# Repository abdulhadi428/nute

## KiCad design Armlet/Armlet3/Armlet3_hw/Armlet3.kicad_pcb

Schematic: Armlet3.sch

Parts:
ANT1: ANT_PCB_MONO
BZ1: BUZZER
C1: 100pF
C2, C4: 1.5pF
C3: 1pF
C5, C8, C62: 3.3pF
C6, C11: 220pF
C7, C9, C12, C15: 10n
C10, C14, C45, C46, C60, C61: 0.1u
C13: 47n
C16, C17: 10pF; CAP_0402
C18, C22, C23, C25, C30, C32, C33, C34, C51, C56, C57: 0.1u; CAP_0603
C19: 1u; CAP_0603
C20, C21, C38, C39, C40, C42, C43, C44, C47, C52: 0.1u; CAP_0402
C24, C31, C35, C41: 10u; CAP_0805
C26, C27, C50: 10u
C28, C48, C64: 1u
C29: DNM
C36, C37, C55: 20pF; CAP_0402
C49, C54: 1u; CAP_0402
C53: 100pF; CAP_0402
C58: 150pF; CAP_0402
C59: 1n; CAP_0402
C63: 6.8pF
D2: LED
D3: PMLL4148
DA1: DNM
DA2: VS1011
DA3: MAX4453
DA4: MCP73832
DA5: NCP583SQ
DD1: CC1101
DD2: STM32F205VX-100
DD3: MMA8452Q
HOLE1, HOLE2: HOLE_METALLED
L1, L6: 18nH; IND_0402
L2, L3, L4, L5: 12nH; IND_0402
L7: 100uH; IND_1812
L8: 15nH; IND_0402
M1: MOTOR
Q1, Q2, Q6: MMBT2222
Q3: TSOP75256
Q4: IRLML9303
Q5: BC848CL
Q7: DNM
R1: 56k
R2, R3: 4k7
R4, R5, R39: 1k
R6, R11: 20
R7, R9: 330k
R8: 10
R10: 2k
R12: 15R; RES_0603
R13: 150; RES_0603
R14: 220R; RES_0402
R15, R16: DNM; RES_0402
R17, R26, R27, R30, R32, R34: 10k; RES_0402
R18: 51R; RES_0402
R19, R29, R35: 1k; RES_0402
R20: 100
R21: 150; RES_0402
R25: 100; RES_0402
R28, R33: 1k; RES_0603
R36: 20k; RES_0402
R37: 330k; RES_0402
R40, R41: 4K7; RES_0402
SW1, SW2, SW3, SW4, SW5, SW6, SW7, SW8, SW9: BUTTON
TP2, TP3: TESTPOINT
VCap1, VCap2: 2.2u; CAP_0402
XL1: CONN_NOKIA_LCD24
XL2: CONN_AUDIO_SIMPLE
XL3, XL4: CONN_4
XL5: CONN_3
XL6: ST_SWD
XL7: CONN_1
XL8: CONN_MICROSD
XL10: USB_MICRO_B
XL11: CONN_NOKIA_BAT
XTAL1: 27MHz; 03225
XTAL2: 12.0MHz; 0532

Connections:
+3.3V: C6.1, C7.1, C8.1, C9.1, C10.1, C11.1, C18.1, C19.1, C20.1, C21.1, C23.1, C25.1, C29.1, C30.1, C31.1, C32.1, C33.1, C34.1, C35.1, C38.1, C39.1, C40.1, C41.1, C42.1, C44.1, C47.1, C49.1, C50.1, C60.1, C64.1, DA1.3 (Vout), DA2.6 (DVDD0), DA2.14 (DVDD1), DA2.19 (DVDD2), DA2.32 (TEST), DA2.38 (AVDD0), DA2.43 (AVDD1), DA2.45 (AVDD2), DA5.3 (Vout), DD1.4 (DVDD), DD1.9 (AVDD), DD1.11 (AVDD), DD1.14 (AVDD), DD1.15 (AVDD), DD1.18 (DGUARD), DD2.6, DD2.11, DD2.19, DD2.22, DD2.28, DD2.50, DD2.75, DD2.100, DD3.1 (VDDIO), DD3.14 (VDD), Q4.2 (S), R2.1, R3.2, R18.1, XL1.3 (VDDI), XL1.7 (PAR/~SPI), XL1.22 (Vdd), XL6.1 (Vdd)
+5V: C27.1, C28.1, DA1.1 (EN), DA1.4 (Vin), DA4.4 (VDD), R15.2, R19.2, XL10.1 (UVcc)
+BATT: BZ1.1, C24.1, C26.1, C48.1, DA4.3 (VBAT), DA5.4 (Vin), M1.2 (-), R7.1, R17.2, R21.2, XL11.1 (+)
/12MHz_Clk: DA2.18 (XTALI), DD2.67
/ACC_IRQ: DD2.17, DD3.11 (INT1)
/Btn1: DD2.81, SW1.2
/Btn2: DD2.82, SW2.2
/Btn3: DD2.84, SW3.2
/Btn4: DD2.85, SW4.2
/Btn5: DD2.88, SW5.2
/Btn6: DD2.55, SW6.2
/Btn7: DD2.56, SW7.2
/Btn8: DD2.57, SW8.2
/Btn9: DD2.58, SW9.2
/Buzzer: DD2.59, R5.1
/BuzzerOut: BZ1.2, Q2.3 (C)
/CC_CS: DD1.7 (CSn), DD2.69
/CC_GDO0: DD1.6 (GDO0), DD2.29, TP2.1
/CC_GDO2: DD1.3 (GDO2), DD2.26, TP3.1
/CC_MISO: DD1.2 (SO(GDO1)), DD2.31
/CC_MOSI: DD1.20 (SI), DD2.32
/CC_SCK: DD1.1 (SCLK), DD2.30
/Charge: DA4.1 (STAT), DD2.18
/I2C_SCL: DD2.92, DD3.4 (SCL), R2.2
/I2C_SDA: DD2.93, DD3.6 (SDA), R3.1
/LCD_BCKLT: DD2.96, R12.2
/LCD_DA0: DD2.97, XL1.6 ((SDA)DA0)
/LCD_DA1: DD2.98, XL1.18 (DA1)
/LCD_DA2: DD2.1, XL1.8 (DA2)
/LCD_DA3: DD2.2, XL1.17 (DA3)
/LCD_DA4: DD2.3, XL1.9 (DA4)
/LCD_DA5: DD2.4, XL1.15 (DA5)
/LCD_DA6: DD2.5, XL1.10 (DA6)
/LCD_DA7: DD2.38, XL1.14 (DA7)
/LCD_DC: DD2.39, XL1.19 ((SCLK)D/~C)
/LCD_RD: DD2.41, XL1.20 (~RD)
/LCD_WR: DD2.40, XL1.5 (~WR)
/LCD_XCS: DD2.42, XL1.11 (CS)
/LCD_XRES: DD2.43, XL1.12 (ResX)
/P_SCL: DD2.47, R40.1, XL3.2 (PM), XL4.2 (PM)
/P_SDA: DD2.48, R41.1, XL3.4, XL4.4
/PeriphPwr: DD2.51, R13.2, R40.2, R41.2
/PeriphPwr1: R13.1, XL3.1, XL4.1
/RF1: DD1.12 (RF_P), L2.2
/RF2: DD1.13 (RF_N), L5.2
/RX2: DD2.87, XL5.3
/SD_CLK: DD2.80, XL8.5 (SCK/CLK)
/SD_CMD: DD2.83, XL8.3 (MOSI/CMD)
/SD_DAT0: DD2.65, XL8.7 (MISO/DAT0)
/SD_DAT1: DD2.66, XL8.8 (DAT1)
/SD_DAT2: DD2.78, XL8.1 (DAT2)
/SD_DAT3: DD2.79, XL8.2 (~SS~/DAT3)
/SD_POWER: DD2.33, Q4.1 (G)
/SD_VDD: C46.1, Q4.3 (D), XL8.4 (VDD)
/SND_C: DA2.42 (GBUF), R8.2, XL2.1 (COM)
/SND_L: DA2.46 (LEFT), R11.2, XL2.3 (L_IN)
/SND_R: DA2.39 (RIGHT), R6.2, XL2.2 (R_IN)
/SWCLK: DD2.76, XL6.2 (SWCLK)
/SWDIO: DD2.72, XL6.4 (SWDIO)
/TX2: DD2.86, XL5.2 (PM)
/UBat_2: DD2.15, R7.2, R9.1
/USB_DM: DD2.70, XL10.2 (D-)
/USB_DP: DD2.71, XL10.3 (D+)
/VS_DREQ: DA2.8 (DREQ), DD2.35
/VS_RST: DA2.3 (~xRESET), DD2.90
/VS_SCLK: DA2.28 (SCLK), DD2.52
/VS_SI: DA2.29 (SI), DD2.54
/VS_SO: DA2.30 (SO), DD2.53
/VS_XCS: DA2.23 (~xCS), DD2.89
/VS_XDCS: DA2.13 (~xDCS~/BSYNC), DD2.95
/Vibro: DD2.45, R4.1
/VibroOut: M1.1 (+), Q1.3 (C)
/XLed1: D2.A, R21.1
/XLed2: D2.C, Q6.3 (C)
/XotarIn: DD2.63, Q3.3 (OUT)
/XotarLED: DD2.64, R39.1
/XotarPower: DD2.34, R20.1
/klNFCModulation: DD2.23, DD2.77
/klNFC_Rx: C55.2, DD2.24, Q5.3 (C), R27.1
/klNFC_Tx: C52.2, DD2.25, R29.1
/klNFC_Vcc: C56.1, DD2.16, R25.2, R27.2, R28.1
AGND: C57.1, DA3.3, DA3.5, R28.2, R33.1, R34.1
GND: C1.1, C4.2, C5.2, C6.2, C7.2, C8.2, C9.2, C10.2, C11.2, C12.1, C13.1, C14.2, C15.1, C16.2, C17.2, C18.2, C19.2, C20.2, C21.2, C22.2, C23.2, C24.2, C25.2, C26.2, C27.2, C28.2, C29.2, C30.2, C31.2, C32.2, C33.2, C34.2, C35.2, C36.2, C37.2, C38.2, C39.2, C40.2, C41.2, C42.2, C43.2, C44.2, C45.2, C46.2, C47.2, C48.2, C49.2, C50.2, C51.2, C56.2, C57.2, C58.2, C59.2, C60.2, C61.2, C62.2, C63.2, C64.2, DA1.2 (GND), DA2.4 (DGND0), DA2.16 (DGND1), DA2.20 (DGND2), DA2.21 (DGND3), DA2.22 (DGND4), DA2.37 (AGND0), DA2.40 (AGND1), DA2.41 (AGND2), DA2.47 (AGND3), DA3.4, DA4.2 (GND), DA5.2 (GND), DD1.16 (GND), DD1.19 (GND), DD1.PAD (GND), DD2.10, DD2.20, DD2.27, DD2.74, DD2.94, DD3.5 (GND), DD3.7 (SA0), DD3.10 (GND), DD3.12 (GND), HOLE1.Hle, HOLE2.Hle, L7.2, Q1.2 (E), Q2.2 (E), Q3.1 (GND), Q3.4 (GND), Q5.2 (E), Q6.2 (E), Q7.2 (E), R1.2, R9.2, R10.2, R16.1, R26.2, R33.2, R35.1, SW1.1, SW2.1, SW3.1, SW4.1, SW5.1, SW6.1, SW7.1, SW8.1, SW9.1, VCap1.2, VCap2.2, XL1.1 (GND), XL1.2 (LED-), XL1.4 (GND), XL1.16 (GND), XL1.21 (GND), XL1.24 (GND), XL1.H (Case), XL2.H, XL3.3, XL4.3, XL5.1, XL6.3 (GND), XL8.6 (GND), XL8.H (Housing), XL10.4 (UGND), XL10.5 (UID), XL10.SHLD, XL11.3 (GND), XTAL1.H, XTAL2.H
unnamed: C53.1, DA3.1, R36.2
unnamed: DA3.2, R29.2, R36.1
unnamed: C52.1, C58.1, L7.1
unnamed: C22.1, DA2.44 (RCAP)
unnamed: C2.1, L3.2, L6.1
unnamed: Q6.1 (B), R39.2
unnamed: C59.1, D3.C, R26.1, R32.1
unnamed: C54.2, D3.A, R35.2
unnamed: C54.1, DA3.7, R37.2
unnamed: DA3.6, R30.2, R37.1
unnamed: Q2.1 (B), R5.2
unnamed: C1.2, L1.1
unnamed: C3.2, C4.1, L5.1, L6.2
unnamed: C2.2, C3.1, L1.2, L2.1
unnamed: Q1.1 (B), R4.2
unnamed: C62.1, L4.1, L8.2
unnamed: ANT1.1, C63.1, L8.1
unnamed: C14.1, DD1.5 (DCOUPL)
unnamed: DD2.61, XL7.1
unnamed: DD1.17 (RBIAS), R1.1
unnamed: C17.1, DD1.10 (XOSC_Q2), XTAL1.2
unnamed: DD2.13, R14.1
unnamed: C15.2, R11.1
unnamed: C12.2, R6.1
unnamed: C13.2, R8.1
unnamed: DA4.5 (PROG), R10.1
unnamed: R12.1, XL1.23 (LED+)
unnamed: DD2.73, VCap2.1
unnamed: C37.1, R14.2, XTAL2.2
unnamed: C36.1, DD2.12, XTAL2.1
unnamed: C16.1, DD1.8 (XOSC_Q1), XTAL1.1
unnamed: C5.1, L3.1, L4.2
unnamed: C61.1, DD3.2 (BYP)
unnamed: C55.1, Q5.1 (B), R32.2
unnamed: DD2.49, VCap1.1
unnamed: DA5.1 (EN), Q7.3 (C), R17.1
unnamed: Q7.1 (B), R15.1, R16.2
unnamed: C45.1, Q3.2 (Vs), R20.2
unnamed: C51.1, DA3.8, R25.1
unnamed: C53.2, R30.1, R34.2
unnamed: C43.1, DD2.21, R18.2
unnamed: DD2.68, R19.1

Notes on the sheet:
Accelerometer I2C addr = 0x1C
USB connect detector
Peripheral I2C Pull-Ups
Pill Connectors
T2C3
USART4 RX
USART4 TX
T2C1/T2ETR
DEBUG TX/RX
USB
Connectors
Radio
CPU
I2C and Accelerometer
Xotar in & out
Vibro & buzzer
klNFC
Nokia battery connector
20pF cap removes remains of carrier
Note AGND here ^^^
Half-Vcc divider
100pF & 10k => f0=160 kHz
Programming
Peripherals usage SDIO - SD Card USB UART2 - debug output UART4 - klNFC SPI1 - CC (Radio) Bus SPI2 - Audio Bus TIM1 Ch4 - Vibro TIM2 Ch3 - klNFC TX TIM2 ETR - klNFC modulation in TIM3 Ch2 - Xotar LED TIM4 Ch1 - Buzzer TIM5 - Xotar Data timings TIM8 Ch1 - Xotar In TIM10 Ch1 - LCD backlight EXTI0 - V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
Audio
Buttons
SD card
I2C pull-ups
3.3V 150mA power regulator
Li-Ion charger 2k => 0.5 A
Battery meter
Power
LCD
Matching circuit
Debug connector

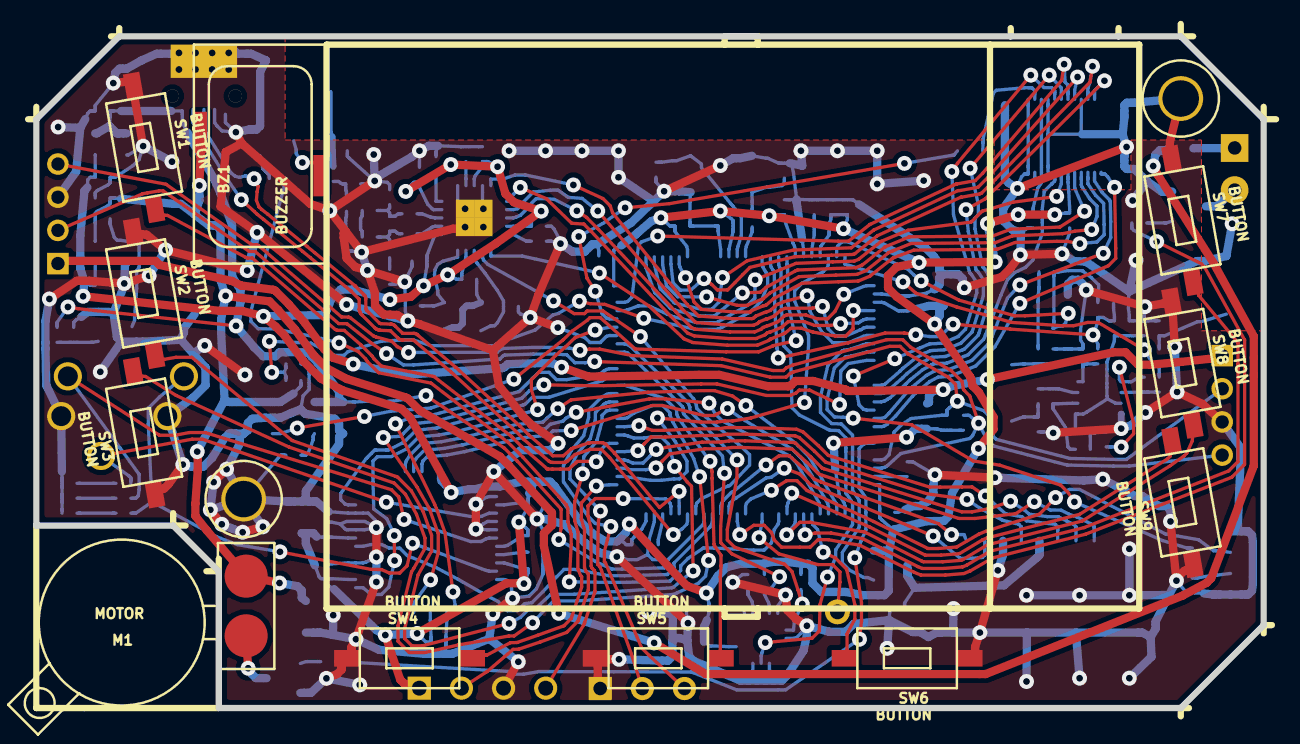
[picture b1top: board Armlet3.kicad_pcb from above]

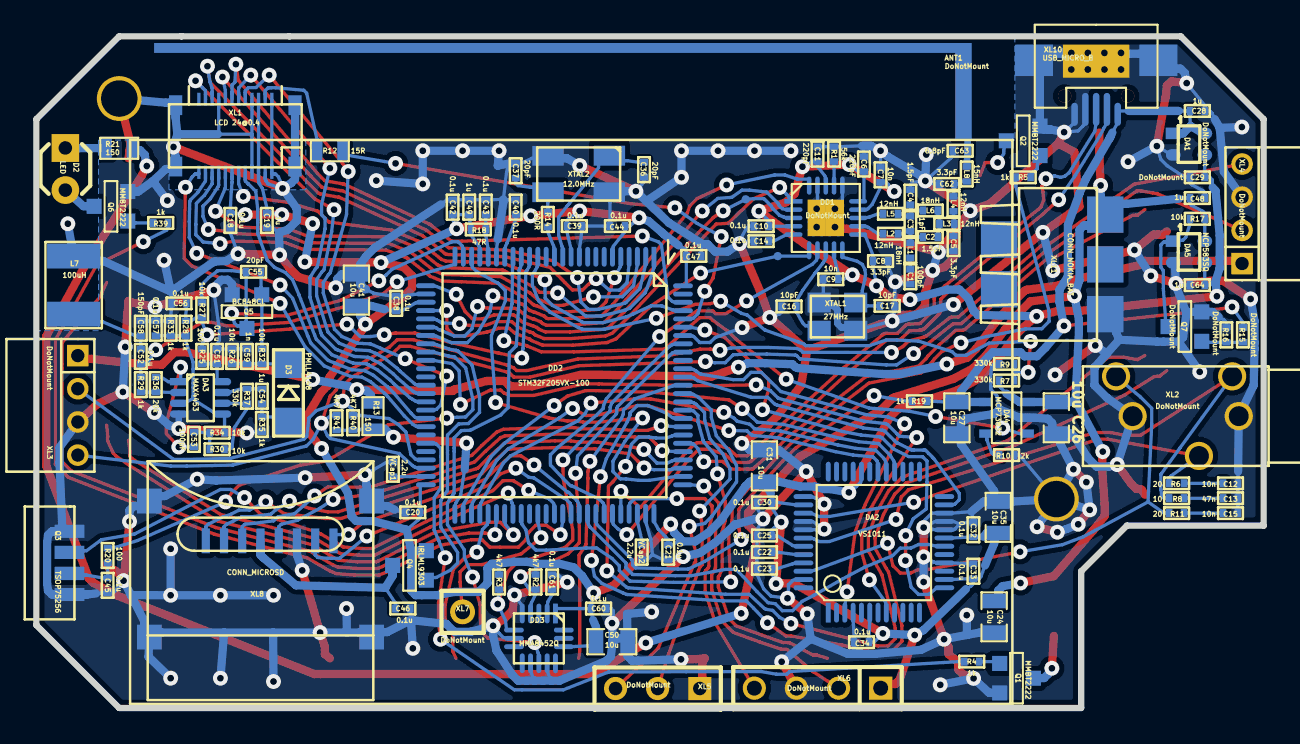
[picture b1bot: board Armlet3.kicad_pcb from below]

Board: 2 copper layers, 74.0 x 40.5 mm, 155 parts (142 on the bottom side), 125 nets.

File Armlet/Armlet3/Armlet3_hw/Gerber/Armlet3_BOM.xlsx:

Document version | Armlet_BOM v.20130328.2012
Reference | Footprint | Value | Item count | Description | Solder Point per cmp | SolderPoint total
Микросхемы
DA1 | SC-82AB | Do not mount
DA2 | LQFP48 | VS1011E-L | 1 | Предоставим в трее | 48 | 48
DA3 | SOT23-8 | MAX4453 | 1 | Предоставим в ленте | 8 | 8
DA4 | SOT23-5 | MCP73832T-2ACI/OT | 1 | Предоставим в ленте | 5 | 5
DA5 | SC-82AB | NCP583SQ33T1G | 1 | Предоставим в ленте | 4 | 4
DD1 | QFN20 | Do not mount
DD2 | LQFP100 | STM32F205VET6-100 | 1 | Предоставим в трее | 100 | 100
DD3 | QFN16_5 | Do not mount
Активные компоненты
Q4 | SOT23 | IRML9303 | 1 | Предоставим в ленте | 3 | 3
Q5 | SOT23 | BC848CL | 1 | Предоставим в ленте | 3 | 3
Q1, Q2, Q6 | SOT23 | MMBT2222 | 3 | Предоставим в ленте | 3 | 9
Q3 | TSOP75256 | TSOP75256 | 1 | Предоставим в ленте | 4 | 4
Q7 | SOT23 | Do not mount
D2 | Выводной | Do not mount
D3 | SOD80C | PMLL4148 | 1 | Предоставим в ленте | 2 | 2
Пассивные компоненты
XTAL1 | SMD3225 | 27MHz | 1 | Предоставим в ленте | 4 | 4
XTAL2 | SMD0532 | 12MHz | 1 | Предоставим в ленте | 4 | 4
Конденсаторы
C3 | CAP_0402 | 1pF NPO | 1 | Предоставим в ленте | 2 | 2
C2, C4 | CAP_0402 | 1.5pF NPO | 2 | Предоставим в ленте | 2 | 4
C5, C8, C62 | CAP_0402 | 3.3pF NPO | 3 | Предоставим в ленте | 2 | 6
C63 | CAP_0402 | 6.8pF NPO | 1 | Предоставим в ленте | 2 | 2
C16, C17 | CAP_0402 | 10pF NPO | 2 | Предоставим в ленте | 2 | 4
C36, C37, C55 | CAP_0402 | 20pF NPO | 3 | Предоставим в ленте | 2 | 6
C1, C53 | CAP_0402 | 100pF NPO | 2 | Предоставим в ленте | 2 | 4
C58 | CAP_0402 | 150pF NPO | 1 | Предоставим в ленте | 2 | 2
C6, C11 | CAP_0402 | 220pF | 2 | Предоставим в ленте | 2 | 4
C59 | CAP_0402 | 1n | 1 | Предоставим в ленте | 2 | 2
C7, C9, C12, C15 | CAP_0402 | 10n | 4 | Предоставим в ленте | 2 | 8
C13 | CAP_0402 | 47n | 1 | Предоставим в ленте | 2 | 2
C10, C14, C18, C20, C21, C22, C23, C25, C30, C32, C33, C34, C38, C39, C40, C42,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 | CAP_0402 | 0.1u | 27 | Предоставим в ленте | 2 | 54
C19, C28, C48, C49, C54, C64 | CAP_0402 | 1u | 6 | Предоставим в ленте | 2 | 12
VCap1, VCap2 | CAP_0402 | 2.2u | 2 | Предоставим в ленте | 2 | 4
C24, C26, C27, C31, C35, C41, C50 | CAP_0805 | 10u | 7 | Предоставим в ленте | 2 | 14
C29 | CAP_0402 | Do not mount
Резисторы
R8 | RES_0402 | 10R | 1 | Предоставим в ленте | 2 | 2
R12 | RES_0603 | 15R | 1 | Предоставим в ленте | 2 | 2
R6, R11 | RES_0402 | 20R | 2 | Предоставим в ленте | 2 | 4
R18 | RES_0402 | 51R | 1 | Предоставим в ленте | 2 | 2
R20, R25 | RES_0402 | 100R | 2 | Предоставим в ленте | 2 | 4
R13, R21 | RES_0603 | 150R | 2 | Предоставим в ленте | 2 | 4
R4, R5, R19, R28, R29, R33, R35, R39 | RES_0402 | 1k | 8 | Предоставим в ленте | 2 | 16
R10 | RES_0402 | 2k | 1 | Предоставим в ленте | 2 | 2
R2, R3, R40, R41 | RES_0402 | 4k7 | 4 | Предоставим в ленте | 2 | 8
R17, R26, R27, R30, R32, R34 | RES_0402 | 10k | 6 | Предоставим в ленте | 2 | 12
R36 | RES_0402 | 20k | 1 | Предоставим в ленте | 2 | 2
R1 | RES_0402 | 56k | 1 | Предоставим в ленте | 2 | 2
R14 | RES_0402 | 220R | 1 | Предоставим в ленте | 2 | 2
R7, R9, R37 | RES_0402 | 330k | 3 | Предоставим в ленте | 2 | 6
R15, R16 | RES_0402 | Do not mount
Индуктивности
L2, L3, L4, L5 | IND_0402 | 12nH | 4 | Предоставим в ленте | 2 | 8
L1, L6 | IND_0402 | 18nH | 2 | Предоставим в ленте | 2 | 4
L7 | IND_1812 | 100uH | 1 | Предоставим в ленте | 2 | 2
L8 | IND_0402 | 15nH | 1 | Предоставим в ленте | 2 | 2
Разъемы
XL1 | LCD_24_04 | LCD 24@0.4 | 1 | Предоставим в ленте | 28 | 28
XL2 |  | Do not mount
XL3, XL4 | PBS2-04R | Do not mount
XL8 | 8pin_cap_fix05 | uSD holder | 1 | Предоставим в ленте | 12 | 12
XL11 | BAT_CONT | Batt contacts | 1 | Предоставим в ленте | 5 | 5
XL10 | USB_MICRO_B | uUSB connector | 1 | Предоставим в ленте | 10 | 10
 |  |  |  |  | Solder points per brd | 463

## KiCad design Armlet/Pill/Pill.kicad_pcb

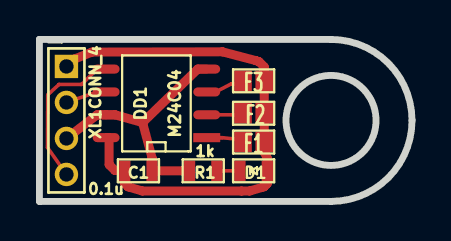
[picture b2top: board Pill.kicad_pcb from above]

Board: 2 copper layers, 20.7 x 9.0 mm, 8 parts (0 on the bottom side), 8 nets.

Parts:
C1: 0.1u; CAP_0603
D1: LED; LED0603
DD1: M24C04; SO8E
F1, F2, F3: FUSE0R; SMD0603_FUSE
R1: 1k; RES_0603
XL1: CONN_4; CONN_2MM_1X4

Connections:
+3.3V: C1.1, D1.A, DD1.8, F1.2, F2.2, F3.2, XL1.1
/1: DD1.1, F1.1
/2: DD1.2, F2.1
/3: DD1.3, F3.1
/I2C_SCL: DD1.6, XL1.2
/I2C_SDA: DD1.5, XL1.4
GND: C1.2, DD1.4, DD1.7, R1.2, XL1.3
unnamed: D1.C, R1.1

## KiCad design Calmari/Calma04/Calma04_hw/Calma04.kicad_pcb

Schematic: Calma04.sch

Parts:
C1, C2, C3, C4, C5: 0.1u; CAP_0603
C6, C8, C12: 0.1u
C7, C9, C11, C13, C14, C15: 10u
C10: 1u; CAP_0603
D1: SS14
DA1: TPS61042
DA2: NCP583SQ
DA3: MCP73832
DD1: STM32F100C4
F1, F2: FUSE0R
HOLE2: HOLE_METALLED
L1: 6.8uH; IND_1210
Q1: ALS-PT19-315C
R1, R2: 330k; RES_0603
R3: 13R; RES_0603
R4: 2k
R5, R6: 10k; RES_0603
R7: 120k; RES_0603
SW1: SWITCH
SW2: BUTTON
TP1: TESTPOINT
XL1: CONN_3
XL2: ST_SWD
XL3, XL4, XL8, XL9, XL10, XL11, XL12, XL13: CONN_1
XL5, XL6: CONN_2
XL7: USB_MICRO_B

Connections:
+3.3V: C2.1, C3.1, C4.1, C5.1, C8.1, C9.1, C10.1, DA2.3 (Vout), DD1.1 (VBAT), DD1.9 (VDDA), DD1.24 (VDD1), DD1.36 (VDD2), DD1.48 (VDD3), F2.2, Q1.1, XL2.1 (Vdd)
+5V: C14.1, DA3.4 (VDD), XL7.1 (UVcc)
+BATT: C6.1, C7.1, C12.1, C13.1, C15.1, DA1.3 (Vin), DA2.1 (EN), DA2.4 (Vin), DA3.3 (VBAT), F1.2, F2.1, L1.2, R2.1, SW1.2, XL10.1, XL11.1
/BAT_IN: F1.1, SW1.1, XL3.1
/BTN: DD1.10 (ADC1-0/WKUP/PA0), SW2.1, XL6.1
/Charge: DA3.1 (STAT), DD1.17 (ADC1-7/T3C2/MOSI1/PA7), XL8.1, XL9.1
/FB: DD1.14 (ADC1-4/DAC1/CK2/PA4), R7.2
/RX: DD1.31 (T1C3/RX1/PA10), XL1.1
/SB_SWCLK: DD1.37 (SWCLK/(JTCK)/(PA14)), XL2.2 (SWCLK)
/SB_SWDAT: DD1.34 (SWDIO/(JTMS)/(PA13)), XL2.4 (SWDIO)
/TX: DD1.30 (T1C2/TX1/PA9), XL1.2 (PM)
GND: C1.2, C2.2, C3.2, C4.2, C5.2, C6.2, C7.2, C8.2, C9.2, C10.2, C11.2, C12.2, C13.2, C14.2, C15.2, DA1.6 (GND), DA1.PAD (GND), DA2.2 (GND), DA3.2 (GND), DD1.8 (VSSA), DD1.23 (VSS1), DD1.35 (VSS2), DD1.44 (BOOT0), DD1.47 (VSS3), HOLE2.Hle, R1.2, R3.2, R4.2, R5.2, SW2.2, XL1.3, XL2.3 (GND), XL4.1, XL6.2 (PM), XL7.4 (UGND), XL7.5 (UID), XL7.SHLD, XL12.1, XL13.1
unnamed: C1.1, DD1.19 (PB1/T3C4/ADC1-9), Q1.2, R5.1
unnamed: DD1.7 (NRST), TP1.1
unnamed: DD1.18 (PB0/T3C3/ADC1-8), R1.1, R2.2
unnamed: DA3.5 (PROG), R4.1
unnamed: DA1.4 (FB), R6.2, R7.1
unnamed: DA1.2 (Rs), R3.1, R6.1
unnamed: DA1.5 (CTRL), DD1.11 (ADC1-1/T2C2/PA1)
unnamed: DA1.1 (LED), XL5.2 (PM)
unnamed: C11.1, D1.C, DA1.7 (OVP), XL5.1
unnamed: D1.A, DA1.8 (SW), L1.1

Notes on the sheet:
-BATTERY
+BATTERY
In case of 2xAA, no LDO is required. Solder fuse instead.
Battery measurement
LEDs (4...8)
Choose capacitor max voltage carefully (30v recommended)
Button
R=252/Iled[mA]
Li-Ion charger 2k => 0.5 A
USB
Connectors for spliting pcb

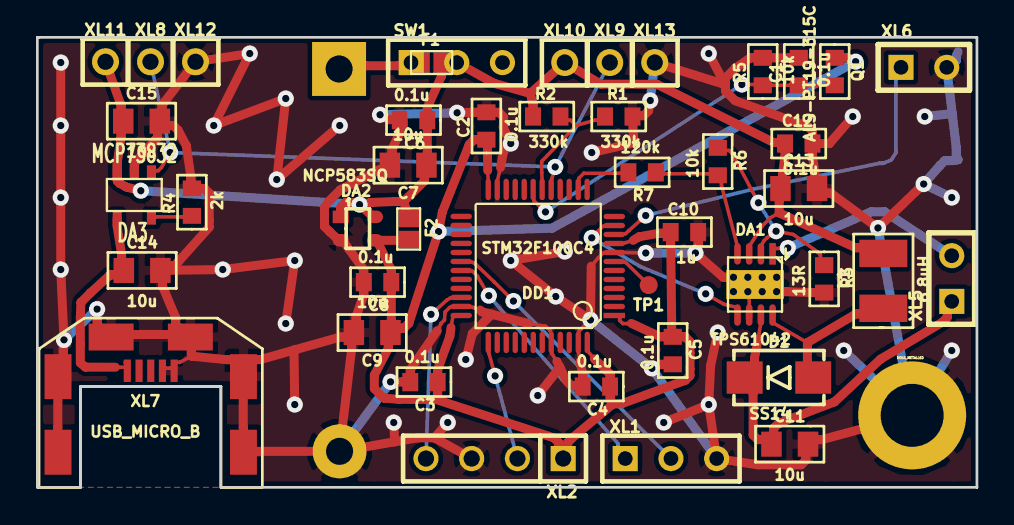
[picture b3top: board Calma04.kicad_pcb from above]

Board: 2 copper layers, 52.2 x 25.0 mm, 48 parts (1 on the bottom side), 22 nets.

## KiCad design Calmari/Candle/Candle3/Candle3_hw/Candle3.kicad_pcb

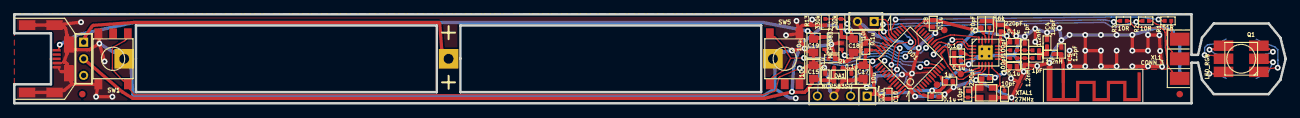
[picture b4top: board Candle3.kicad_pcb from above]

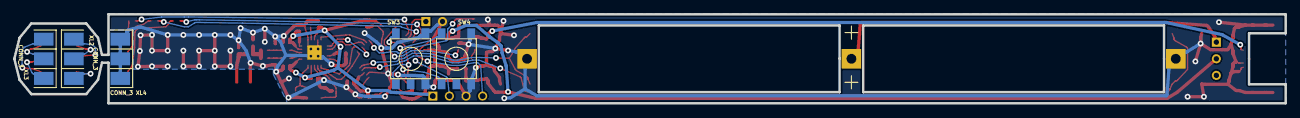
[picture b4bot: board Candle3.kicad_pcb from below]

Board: 2 copper layers, 194.4 x 13.6 mm, 63 parts (5 on the bottom side), 43 nets.

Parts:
ANT1: ANT_GENERAL; ANT_2400_MEANDER
C1, C3: 100pF; CAP_0402
C2, C6: 1pF; CAP_0402
C4: 1.8pF; CAP_0402
C5: 1.5pF; CAP_0402
C7, C13: 10pF; CAP_0402
C8, C9, C10, C11, C14, C16, C41, C51, C111, C141: 0.1u; CAP_0402
C12: 1u; CAP_0402
C15, C17, C18, C19: 10u; CAP_0805
C91, C151, C181: 220pF; CAP_0402
DA1: NCP583SQ; SC82AB
DA2: MCP73832; SOT23-5
DD1: STM32F100C4; LQFP48
DD2: CC2500; QFN20
L1, L2, L3: 1.2nH; IND_0402
Q1: LED_RGB; LED_HH5050_RGB
R1: 51R; RES_0402
R2, R3: 10R; RES_0402
R4: 2k; RES_0402
R6, R13: 330k; RES_0402
R171: 56k; RES_0402
RP1, RP2, RP3: REFPOINT; REF_POINT_1MM
SW1: SWITCH; SIL-3
SW2, SW3, SW4, SW5: BUTTON; BUTTON_6x6SMD
TP1, TP2: TESTPOINT; TESTPOINT_1MM
XL1, XL2, XL3, XL4: CONN_3; CONN_SOLDER3
XL5: ST_SWD; SIL-4
XL6: USB_MICRO_B; USBmicro_MOLEX_WM17142
XL7: CONN_2; SIL-2
XL9, XL15, XL16: CONN_1; SIL1_SQUARE_1MM5
XTAL1: 27MHz; CRYSTAL_03225C4

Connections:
+3.3V: C8.1, C9.1, C10.1, C11.1, C12.1, C16.1, C17.1, C41.1, C91.1, C111.1, C141.1, C151.1, C181.1, DA1.3, DD1.1, DD1.9, DD1.24, DD1.36, DD1.48, DD2.4, DD2.9, DD2.11, DD2.14, DD2.15, DD2.18, XL5.1
+5V: C19.1, DA2.4, XL6.1
+BATT: C14.1, C15.1, C18.1, DA1.1, DA1.4, DA2.3, R6.1, SW1.2
/Ant1: C1.1, DD2.12
/Ant2: C3.1, DD2.13
/BATTERY_PLUS: SW1.1, XL9.1
/BTN_DOWN: DD1.43, SW4.2
/BTN_PWR: DD1.10, SW2.2
/BTN_TX: DD1.11, SW5.2
/BTN_UP: DD1.42, SW3.2
/CC_CS: DD1.13, DD2.7
/CC_GDO0: DD1.14, DD2.6, TP1.1
/CC_MISO: DD1.16, DD2.2
/CC_MOSI: DD1.17, DD2.20
/CC_SCK: DD1.15, DD2.1
/Charge: DA2.1, DD1.25
/LED_B: DD1.32, R3.1
/LED_G: DD1.31, R2.1
/LED_R: DD1.29, R1.1
/SWCLK: DD1.37, XL5.2
/SWDIO: DD1.34, XL5.4
GND: ANT1.2, C4.2, C5.2, C6.2, C7.2, C8.2, C9.2, C10.2, C11.2, C12.2, C13.2, C14.2, C15.2, C16.2, C17.2, C18.2, C19.2, C41.2, C51.2, C91.2, C111.2, C141.2, C151.2, C181.2, DA1.2, DA2.2, DD1.8, DD1.23, DD1.35, DD1.44, DD1.47, DD2.16, DD2.19, DD2.PAD, L1.1, R4.2, R13.2, R171.2, SW2.1, SW3.1, SW4.1, SW5.1, XL4.1, XL4.2, XL4.3, XL5.3, XL6.4, XL6.5, XL6.SHLD, XL7.2, XL15.1, XL16.1, XTAL1.H
unnamed: DA2.5, R4.1
unnamed: Q1.RA, XL2.1
unnamed: Q1.GC, XL3.2
unnamed: Q1.RC, XL3.1
unnamed: Q1.BC, XL3.3
unnamed: Q1.GA, XL2.2
unnamed: Q1.BA, XL2.3
unnamed: R1.2, XL1.1
unnamed: R2.2, XL1.2
unnamed: R3.2, XL1.3
unnamed: C1.2, C2.1, L1.2
unnamed: DD1.7, TP2.1
unnamed: C3.2, C6.1, L3.2
unnamed: ANT1.1, C5.1, L2.1
unnamed: C2.2, C4.1, L2.2, L3.1
unnamed: DD1.30, XL7.1
unnamed: C13.1, DD2.10, XTAL1.2
unnamed: C7.1, DD2.8, XTAL1.1
unnamed: DD1.18, R6.2, R13.1
unnamed: DD2.17, R171.1
unnamed: C51.1, DD2.5

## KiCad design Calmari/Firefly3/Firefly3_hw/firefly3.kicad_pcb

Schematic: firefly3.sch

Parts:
C1, C2, C3, C4, C5: 0.1u; CAP_0603
C6, C8: 0.1u
C7, C9: 10u
C10: 1u; CAP_0603
D1: BAT54WS; SOD323
D2: LED
DA1: NCP1400
DD1: STM32F100C4
F1: FUSE0R
L1: 22uH
Q1: ALS-PT19-315C
Q2: LED_RGB 5050
R1, R3, R4: 51R; RES_0603
R2, R5: 10k; RES_0603
SW1: SWITCH
TP1: TESTPOINT
XL1: CONN_3
XL2: ST_SWD
XL3, XL4, XL6: CONN_1
XL5: CONN_8

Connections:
+3.3V: C2.1, C3.1, C4.1, C5.1, C8.1, C9.1, C10.1, D1.C, DA1.1 (CE), DA1.2 (OUT), DD1.1 (VBAT), DD1.9 (VDDA), DD1.24 (VDD1), DD1.36 (VDD2), DD1.48 (VDD3), Q1.1, XL2.1 (Vdd)
+BATT: C6.1, C7.1, F1.2, L1.2, R2.1, SW1.2
/2: DD1.43 (PB7/SDA1/T17C1N), XL5.2
/3: DD1.42 (PB6/SCL1/T16C1N), XL5.3
/4: DD1.39 ((PB3)/JTDO/(T2C2)), XL5.4
/5: DD1.14 (ADC1-4/DAC1/CK2/PA4), XL5.5
/6: DD1.15 (ADC1-5/DAC2/SCK1/PA5), XL5.6
/7: DD1.16 (ADC1-6/T3C1/MISO1/PA6), XL5.7
/8: DD1.17 (ADC1-7/T3C2/MOSI1/PA7), XL5.8
/BAT_IN: F1.1, SW1.1, XL3.1
/Lout: D1.A, DA1.5 (LX), L1.1
/RX: DD1.31 (T1C3/RX1/PA10), XL1.1
/SB_SWCLK: DD1.37 (SWCLK/(JTCK)/(PA14)), XL2.2 (SWCLK)
/SB_SWDAT: DD1.34 (SWDIO/(JTMS)/(PA13)), XL2.4 (SWDIO)
/TX: DD1.30 (T1C2/TX1/PA9), XL1.2 (PM)
GND: C1.2, C2.2, C3.2, C4.2, C5.2, C6.2, C7.2, C8.2, C9.2, C10.2, D2.C, DA1.4 (GND), DD1.8 (VSSA), DD1.23 (VSS1), DD1.35 (VSS2), DD1.44 (BOOT0), DD1.47 (VSS3), Q2.BC (B), Q2.GC (G), Q2.RC, R5.2, XL1.3, XL2.3 (GND), XL4.1, XL5.1, XL6.1
unnamed: DD1.18 (PB0/T3C3/ADC1-8), R2.2
unnamed: DD1.7 (NRST), TP1.1
unnamed: C1.1, DD1.19 (PB1/T3C4/ADC1-9), Q1.2, R5.1
unnamed: Q2.BA, R4.2
unnamed: DD1.13 (ADC1-3/T2C4/T15C2/RX2/PA3), R3.1
unnamed: DD1.12 (ADC1-2/T2C3/T15C1/TX2/PA2), R1.1
unnamed: DD1.11 (ADC1-1/T2C2/PA1), R4.1
unnamed: D2.A, Q2.RA, R1.2
unnamed: Q2.GA, R3.2

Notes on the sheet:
-BATTERY
+BATTERY

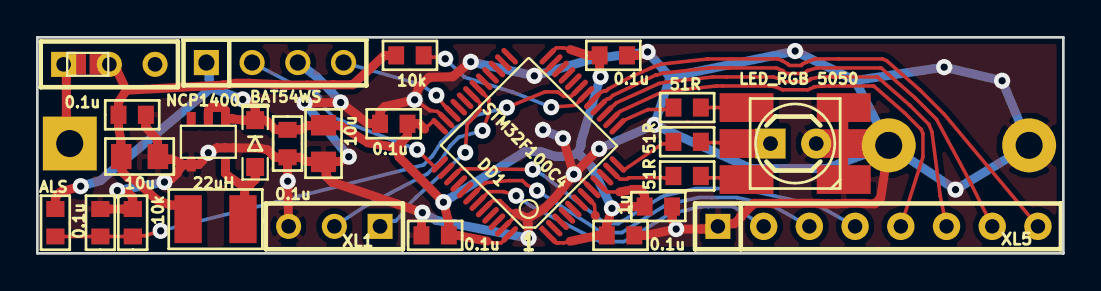
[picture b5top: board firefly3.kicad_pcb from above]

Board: 2 copper layers, 57.0 x 12.0 mm, 31 parts (0 on the bottom side), 25 nets.

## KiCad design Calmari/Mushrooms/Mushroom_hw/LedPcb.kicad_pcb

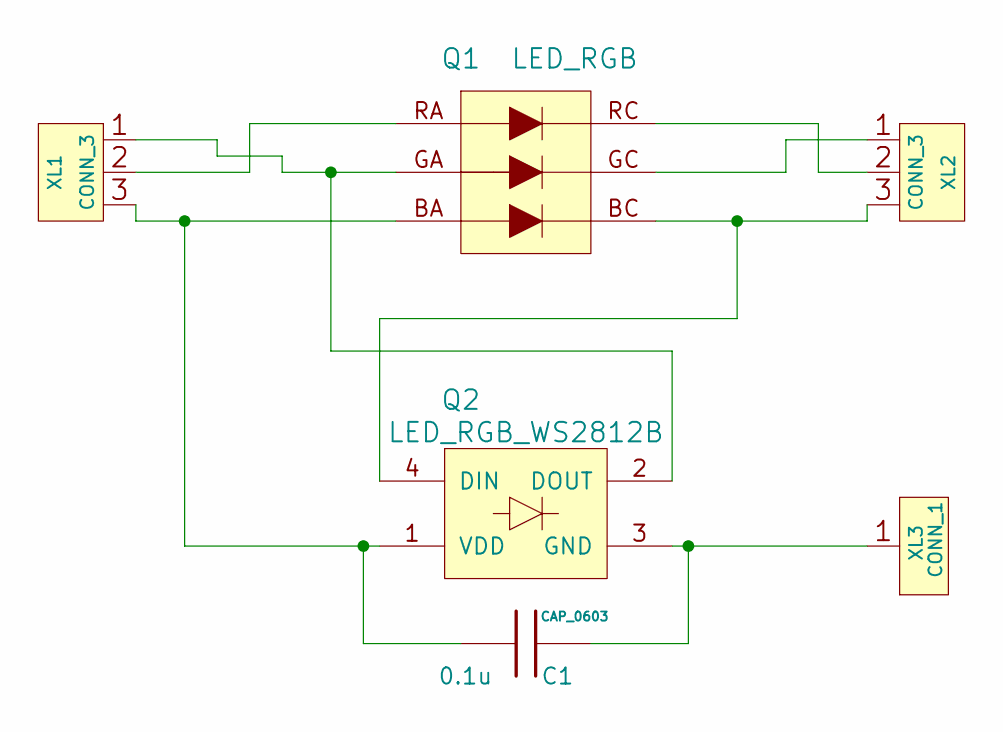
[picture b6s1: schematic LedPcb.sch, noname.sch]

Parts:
C1: 0.1u; CAP_0603
Q1: LED_RGB
Q2: LED_RGB_WS2812B
XL1, XL2: CONN_3
XL3: CONN_1

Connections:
unnamed: Q1.GA, Q2.2 (DOUT), XL1.1
unnamed: Q1.BC (B), Q2.4 (DIN), XL2.3
unnamed: Q1.RA, XL1.2 (PM)
unnamed: Q1.RC, XL2.2 (PM)
unnamed: Q1.GC (G), XL2.1
unnamed: C1.1, Q1.BA, Q2.1 (VDD), XL1.3
unnamed: C1.2, Q2.3 (GND), XL3.1

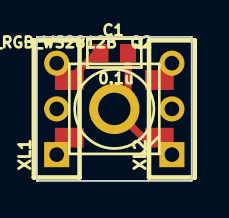
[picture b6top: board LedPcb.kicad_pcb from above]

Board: 2 copper layers, 8.6 x 8.0 mm, 6 parts (1 on the bottom side), 7 nets.

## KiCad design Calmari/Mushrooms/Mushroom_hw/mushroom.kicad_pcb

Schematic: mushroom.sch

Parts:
ANT1: ANT_PCB_NOCNTR
B1, B2, B3: BAT
C1, C6, C12, C14, C19, C20, C23, C24, C26: 0.1u
C2, C8, C11, C13, C15, C16, C21, C28: 10u
C3: 10u; CAP_0603
C4, C5, C7, C29, C30, C31: 0.1u; CAP_0603
C9: 10n; CAP_0603
C10: 1u; CAP_0603
C17, C18: 10pF; CAP_0603
C22, C25, C27: 220pF
D1, D2, D3: SS14
DA1, DA3, DA4: TPS61042
DA2: NCP583SQ
DD1: STM32L151CXTX
DD2: CC2500
F1, F2, F3, F4, F5, F6, F7, F8, F9, F10, F11, F12, F13, F14, F15, F16, F17, F18, F19, F20: FUSE0R
HOLE1, HOLE2, HOLE3, HOLE4: HOLE_METALLED
L1, L2, L3: 6.8uH; IND_1210
Q1, Q3, Q6: LED_RGB_WS2812B
Q2, Q4, Q5: LED_RGB
R1, R2: 4K7; RES_0402
R3, R8, R15: 100k
R4: 150; RES_0402
R5, R11, R16: 10k; RES_0603
R6, R12, R17: 13R; RES_0603
R7, R13, R18: 120k; RES_0603
R9, R10: 390k; RES_0603
R14: 56k
R19, R20, R21: 51R; RES_0603
RP1, RP2: REFPOINT
SW1: SWITCH_H
TP1, TP2, TP3: TESTPOINT
XL1, XL5, XL6, XL8, XL9, XL10, XL12, XL13, XL14, XL16, XL17, XL18, XL20, XL21, XL22, XL24: CONN_3
XL2: ST_SWD
XL3: CONN_4
XL4: CONN_4
XL7, XL11, XL15, XL19, XL23: CONN_1
XTAL1: 27MHz; 03225

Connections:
+3.3V: C3.1, C4.1, C5.1, C7.1, C9.1, C10.1, C12.1, C13.1, C22.1, C23.1, C24.1, C25.1, C26.1, C27.1, DA2.3 (Vout), DD1.1, DD1.9, DD1.24, DD1.36, DD1.48, DD2.4 (DVDD), DD2.9 (AVDD), DD2.11 (AVDD), DD2.14 (AVDD), DD2.15 (AVDD), DD2.18 (DGUARD), XL2.1 (Vdd)
+BATT: C1.1, C2.1, C6.1, C8.1, C14.1, C15.1, C20.1, C21.1, C29.1, C30.1, C31.1, DA1.3 (Vin), DA2.1 (EN), DA2.4 (Vin), DA3.3 (Vin), DA4.3 (Vin), L1.2, L2.2, L3.2, Q1.1 (VDD), Q3.1 (VDD), Q6.1 (VDD), R9.1, SW1.2, XL6.2 (PM), XL10.2 (PM), XL14.2 (PM), XL18.2 (PM), XL22.2 (PM)
/Ant: ANT1.1, ANT1.2, DD2.12 (RF_P), DD2.13 (RF_N)
/BAT_IN: B3.A, SW1.1
/BLUE_N: DA4.1 (LED), F6.1, F10.1, F15.1, F20.2, Q5.BC (B), XL24.3
/BLUE_P: C28.1, D3.C, DA4.7 (OVP), Q2.BA, R21.2, XL5.3
/BLUE_PWM: DA4.5 (CTRL), DD1.41, R15.1, R21.1
/BRIGHTNESS: DD1.14, R7.2, R13.2, R18.2
/CC_CS: DD1.12, DD2.7 (CSn)
/CC_GDO0: DD1.13, DD2.6 (GDO0), TP2.1
/CC_GDO2: DD1.11, DD2.3 (GDO2), TP3.1
/CC_MISO: DD1.16, DD2.2 (SO(GDO1))
/CC_MOSI: DD1.17, DD2.20 (SI)
/CC_SCK: DD1.15, DD2.1 (SCLK)
/DIN0: DD1.28, Q1.4 (DIN), XL6.1
/DIN1: XL6.3, XL10.1
/DIN2: XL10.3, XL14.1
/DIN3: XL14.3, XL18.1
/DIN4: XL18.3, XL22.1
/GREEN_N: DA3.1 (LED), F5.1, F9.1, F16.1, F19.2, Q5.GC (G), XL24.2 (PM)
/GREEN_P: C16.1, D2.C, DA3.7 (OVP), Q2.GA, R20.2, XL5.2 (PM)
/GREEN_PWM: DA3.5 (CTRL), DD1.19, R8.1, R20.1
/P_SCL: DD1.45, R1.1, XL3.2 (PM)
/P_SDA: DD1.46, R2.1, XL3.4
/PeriphPwr: DD1.43, R1.2, R2.2, R4.2
/PeriphPwr1: R4.1, XL3.1
/RED_N: DA1.1 (LED), F4.1, F8.1, F17.1, F18.2, Q5.RC, XL24.1
/RED_P: C11.1, D1.C, DA1.7 (OVP), Q2.RA, R19.2, XL5.1
/RED_PWM: DA1.5 (CTRL), DD1.18, R3.1, R19.1
/SWCLK: DD1.37, XL2.2 (SWCLK)
/SWDIO: DD1.34, XL2.4 (SWDIO)
/UART_RX: DD1.31, XL1.3
/UART_TX: DD1.30, XL1.2 (PM)
GND: B1.C, C1.2, C2.2, C3.2, C4.2, C5.2, C6.2, C7.2, C8.2, C9.2, C10.2, C11.2, C12.2, C13.2, C14.2, C15.2, C16.2, C17.2, C18.2, C19.2, C20.2, C21.2, C22.2, C23.2, C24.2, C25.2, C26.2, C27.2, C28.2, C29.2, C30.2, C31.2, DA1.6 (GND), DA1.PAD (GND), DA2.2 (GND), DA3.6 (GND), DA3.PAD (GND), DA4.6 (GND), DA4.PAD (GND), DD1.8, DD1.23, DD1.35, DD1.44, DD1.47, DD2.16 (GND), DD2.19 (GND), DD2.PAD (GND), F1.1, F2.1, F3.1, F7.1, F11.1, F18.1, F19.1, F20.1, HOLE1.Hle, HOLE2.Hle, HOLE3.Hle, HOLE4.Hle, Q1.3 (GND), Q3.3 (GND), Q6.3 (GND), R3.2, R6.2, R8.2, R10.2, R12.2, R14.2, R15.2, R17.2, SW1.H, XL1.1, XL2.3 (GND), XL3.3, XL4.4, XTAL1.H
unnamed: C17.1, DD2.8 (XOSC_Q1), XTAL1.1
unnamed: C18.1, DD2.10 (XOSC_Q2), XTAL1.2
unnamed: DA1.4 (FB), R5.2, R7.1
unnamed: DA1.2 (Rs), R5.1, R6.1
unnamed: DD1.10, R9.2, R10.1
unnamed: C19.1, DD2.5 (DCOUPL)
unnamed: B1.A, B2.C
unnamed: DD2.17 (RBIAS), R14.1
unnamed: DA3.2 (Rs), R11.1, R12.1
unnamed: DA3.4 (FB), R11.2, R13.1
unnamed: D2.A, DA3.8 (SW), L2.1
unnamed: D1.A, DA1.8 (SW), L1.1
unnamed: F14.2, Q2.RC, Q4.RA
unnamed: F13.2, Q2.GC (G), Q4.GA
unnamed: XL12.3, XL13.3
unnamed: XL12.2 (PM), XL13.2 (PM)
unnamed: XL12.1, XL13.1
unnamed: XL8.3, XL9.3
unnamed: XL8.2 (PM), XL9.2 (PM)
unnamed: XL8.1, XL9.1
unnamed: F11.2, XL23.1
unnamed: F10.2, XL20.3, XL21.3
unnamed: DD1.25, XL4.3
unnamed: DD1.21, XL4.1
unnamed: DD1.22, XL4.2 (PM)
unnamed: B2.A, B3.C
unnamed: F12.2, Q2.BC (B), Q4.BA
unnamed: F14.1, F17.2, Q4.RC, Q5.RA
unnamed: F13.1, F16.2, Q4.GC (G), Q5.GA
unnamed: F12.1, F15.2, Q4.BC (B), Q5.BA
unnamed: DD1.7, TP1.1
unnamed: Q3.2 (DOUT), Q6.4 (DIN)
unnamed: Q1.2 (DOUT), Q3.4 (DIN)
unnamed: DA4.2 (Rs), R16.1, R17.1
unnamed: DA4.4 (FB), R16.2, R18.1
unnamed: D3.A, DA4.8 (SW), L3.1
unnamed: F6.2, XL16.3, XL17.3
unnamed: F9.2, XL20.2 (PM), XL21.2 (PM)
unnamed: F8.2, XL20.1, XL21.1
unnamed: F5.2, XL16.2 (PM), XL17.2 (PM)
unnamed: F4.2, XL16.1, XL17.1
unnamed: F1.2, XL7.1
unnamed: F2.2, XL11.1
unnamed: F3.2, XL15.1
unnamed: F7.2, XL19.1

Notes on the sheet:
UART
Programming
CPU
Power
Just Pins
Battery measurement
Choose capacitor max voltage carefully (30v recommended)
R=252/Iled[mA]
Place resistors and fuses if single LED is required
For WS2812B
For RGB
Solder fuses for WS2812B
Peripheral I2C Pull-Ups
Pill Connector
Pill

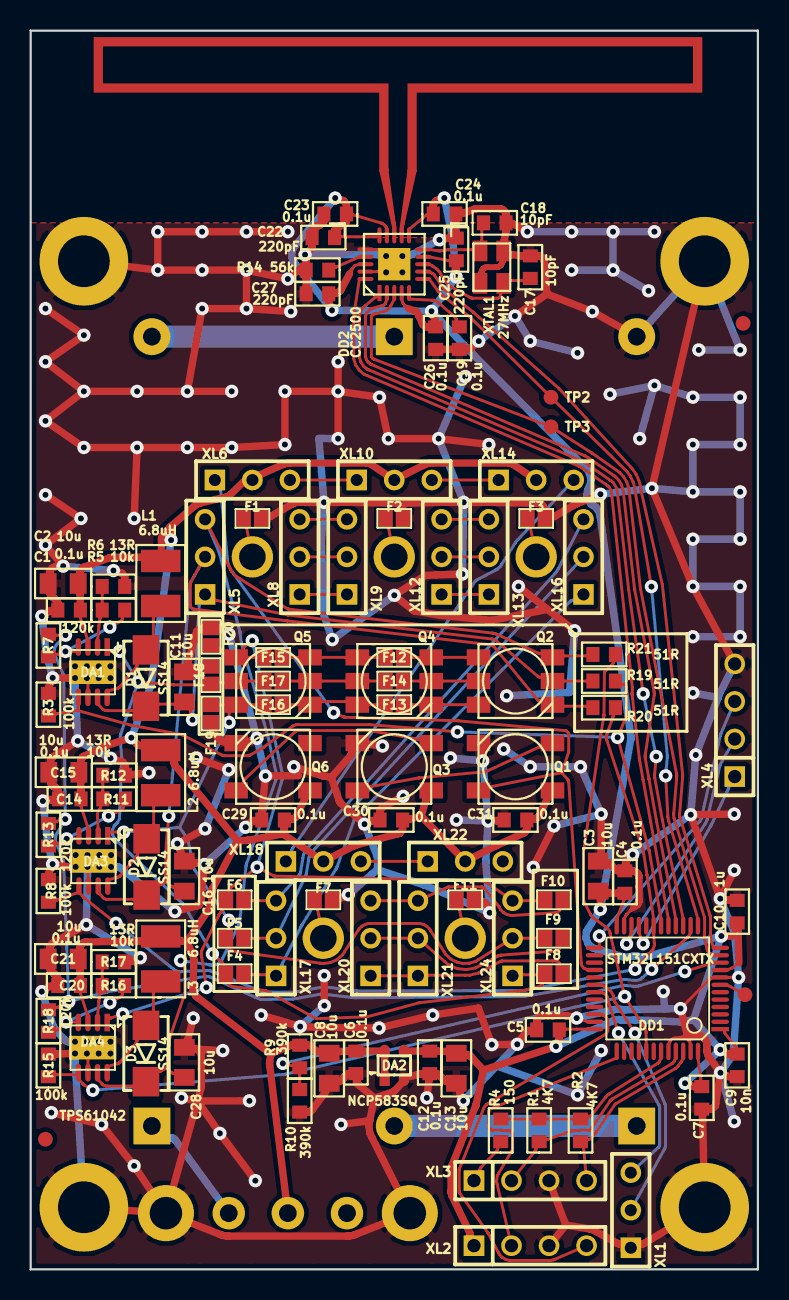
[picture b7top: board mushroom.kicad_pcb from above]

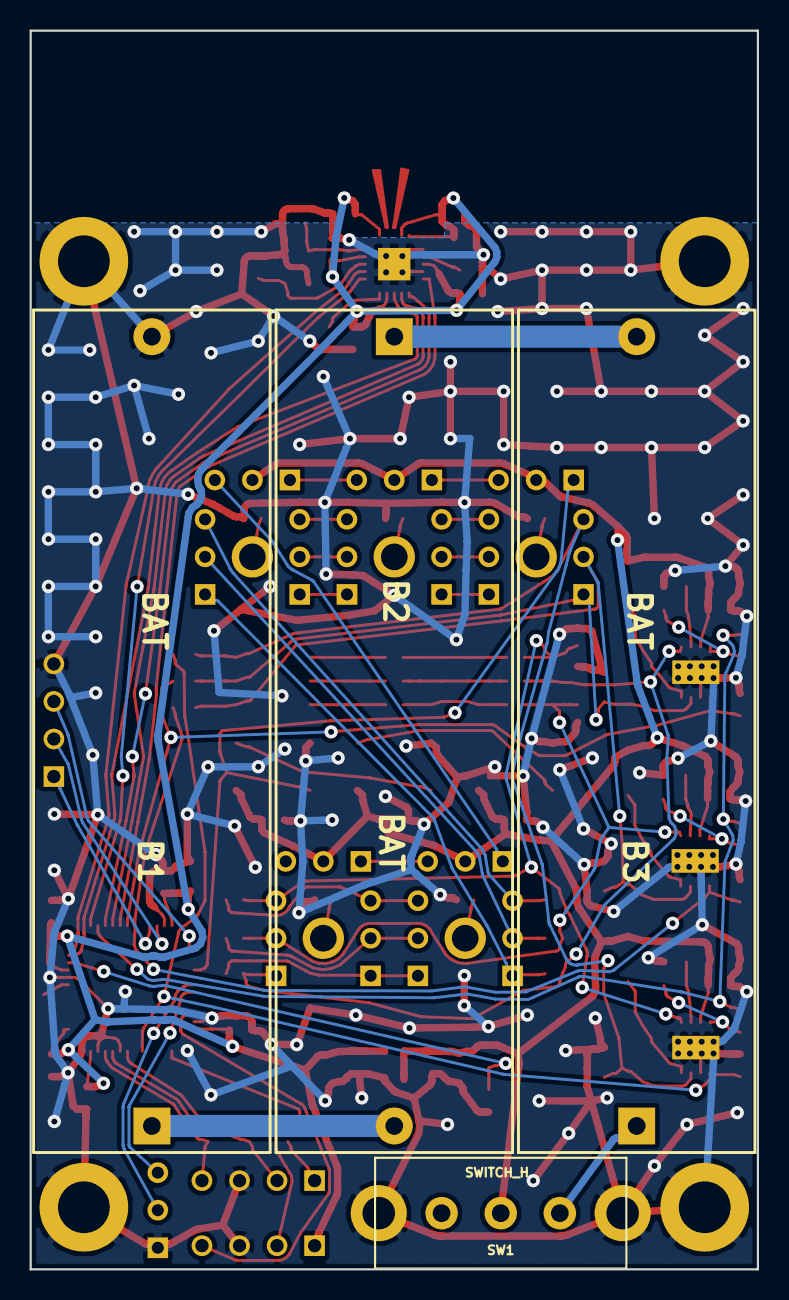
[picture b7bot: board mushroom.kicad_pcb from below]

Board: 2 copper layers, 49.2 x 83.8 mm, 129 parts (4 on the bottom side), 79 nets.

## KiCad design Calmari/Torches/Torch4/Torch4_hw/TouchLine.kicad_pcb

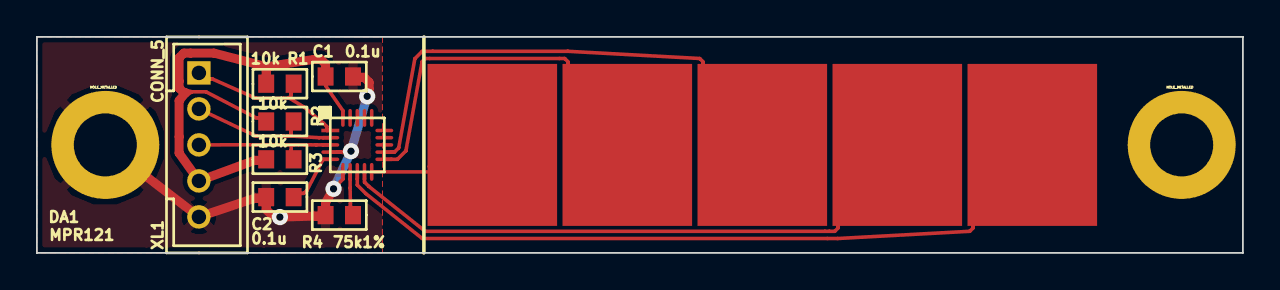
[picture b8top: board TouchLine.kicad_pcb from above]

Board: 2 copper layers, 67.0 x 12.0 mm, 15 parts (0 on the bottom side), 12 nets.

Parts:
C1, C2: 0.1u; CAP_0603
DA1: MPR121; QFN20_04PITCH
HOLE1, HOLE2: HOLE_METALLED; Hole3_5_out6mm
R1, R2, R3: 10k; RES_0603
R4: 75k1%; RES_0603
SNSP1, SNSP2, SNSP3, SNSP4, SNSP5: SENSORPAD; SENSOR_PAD_7D2_9
XL1: CONN_5; CONN_MW_5M

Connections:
+3.3V: C1.1, DA1.20, R1.1, R2.1, R3.1, XL1.4
/IRQ: DA1.1, R1.2, XL1.1
/SCL: DA1.2, R2.2, XL1.2
/SDA: DA1.3, R3.2, XL1.3
GND: C1.2, C2.2, DA1.4, DA1.6, HOLE2.Hle, R4.2, XL1.5
unnamed: C2.1, DA1.5
unnamed: DA1.7, R4.1
unnamed: DA1.8, SNSP1.1
unnamed: DA1.9, SNSP2.1
unnamed: DA1.10, SNSP3.1
unnamed: DA1.12, SNSP5.1
unnamed: DA1.11, SNSP4.1
